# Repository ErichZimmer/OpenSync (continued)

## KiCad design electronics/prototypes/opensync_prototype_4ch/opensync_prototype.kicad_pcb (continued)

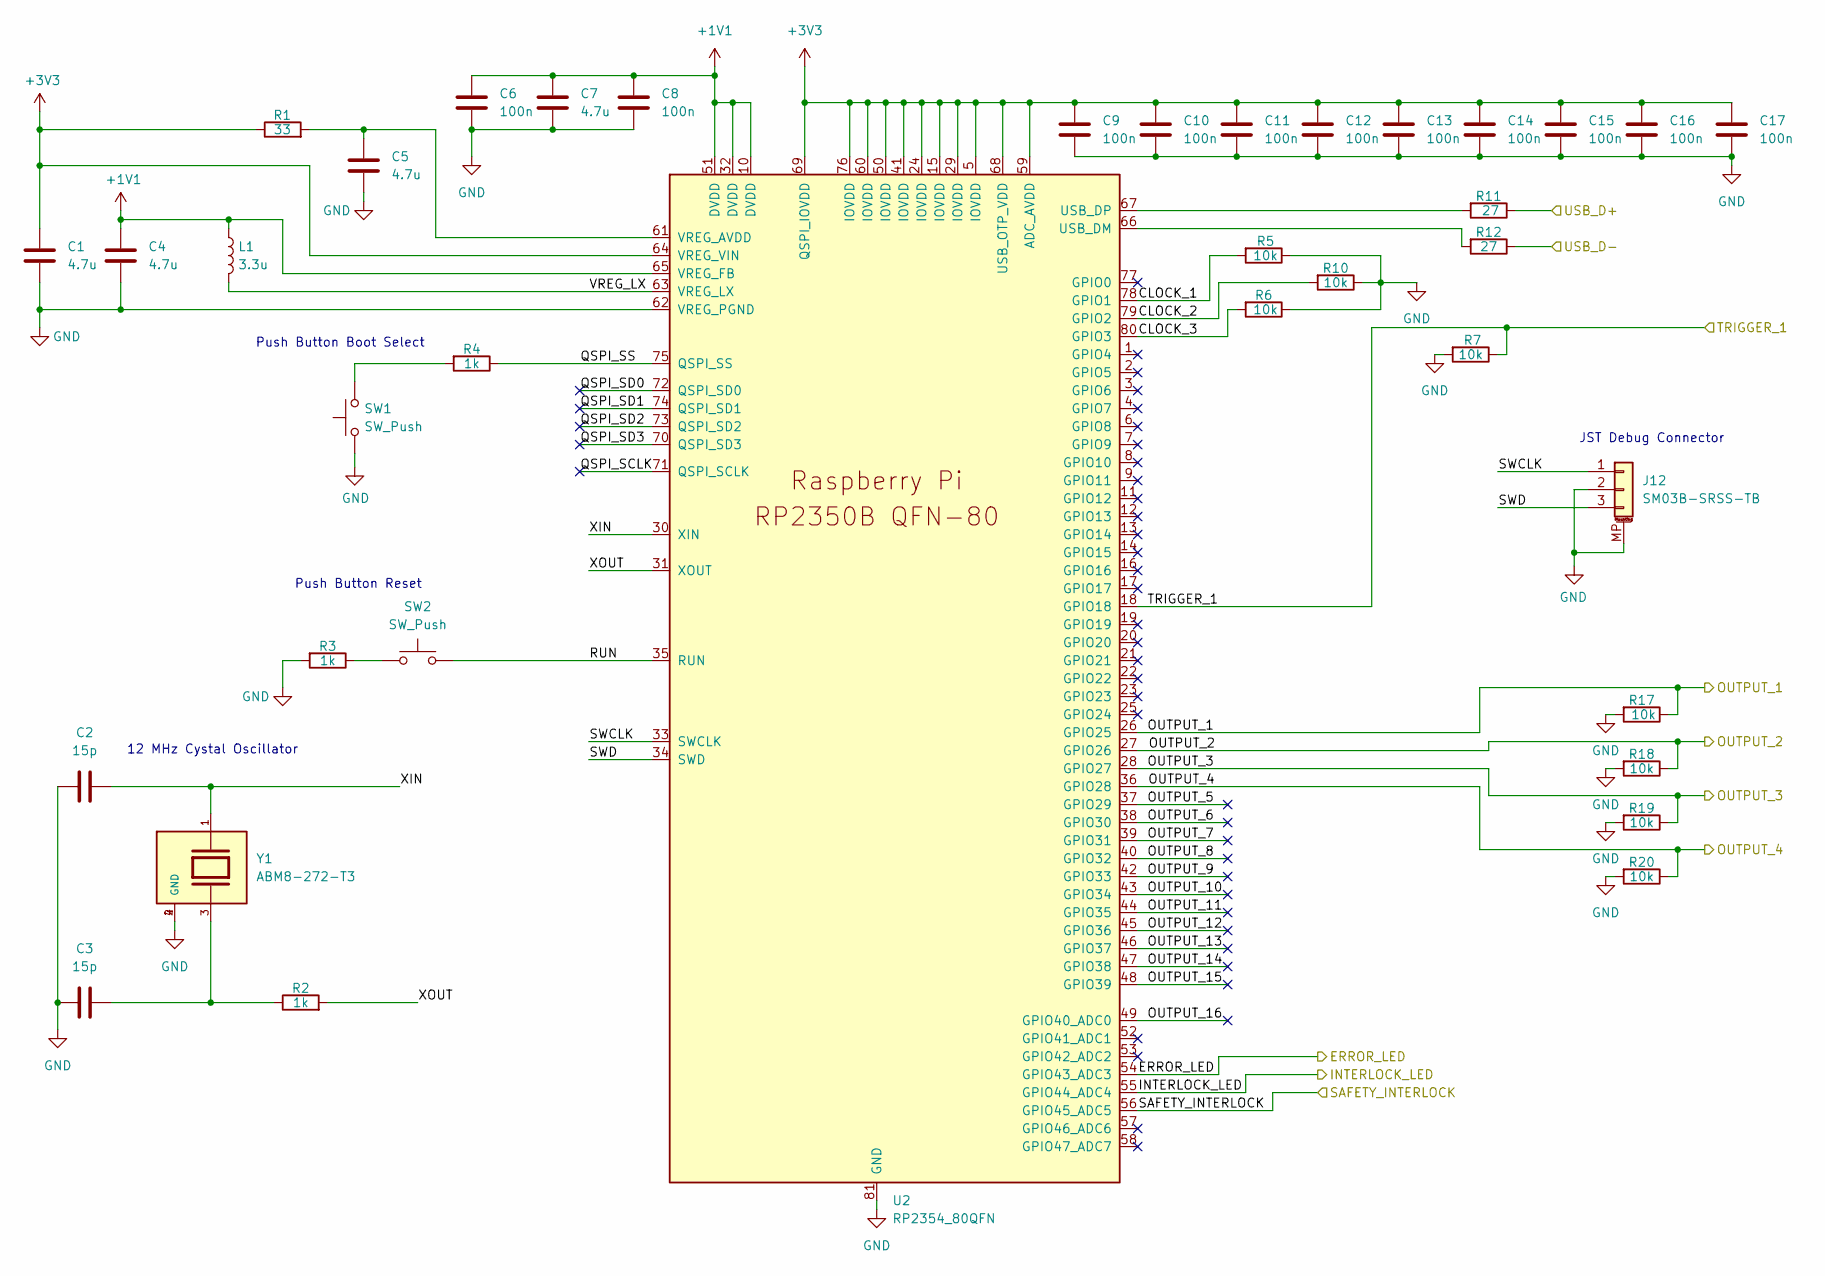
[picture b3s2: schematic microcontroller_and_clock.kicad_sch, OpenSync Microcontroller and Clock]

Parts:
C1, C4, C5: 4.7u; C_0402_1005Metric_small_pads; LCSC C326586
C2, C3: 15p; C_0402_1005Metric_small_pads; LCSC C326803
C6, C8, C9, C10, C11, C12, C13, C14, C15, C16, C17: 100n; C_0402_1005Metric_small_pads; LCSC C60474
C7: 4.7u; C_0402_1005Metric_small_pads; LCSC C60474
J12: SM03B-SRSS-TB; JST_SH_SM03B-SRSS-TB_1x03-1MP_P1.00mm_Horizontal; LCSC C160403
L1: 3.3u; L_pol_2016; LCSC C42411119
R1: 33; R_0402_1005Metric; LCSC C844506
R2, R3, R4: 1k; R_0402_1005Metric; LCSC C313354
R5, R6, R7, R10, R17, R18, R19, R20: 10k; R_0402_1005Metric; LCSC C71617
R11, R12: 27; R_0402_1005Metric; LCSC C4162575
SW1, SW2: SW_Push; SW_Push_1P1T_NO_Vertical_Wuerth_434133025816; LCSC C5504987
U2: RP2354_80QFN; RP2350-QFN-80-1EP_10x10_P0.4mm_EP3.4x3.4mm_ThermalVias; LCSC C39843328
Y1: ABM8-272-T3; XTAL_ABM8-272-T3; PARTREV 07-29-20; LCSC C20625731

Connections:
+1V1: C4.1, C6.1, C7.1, C8.1, L1.1, U2.10 (DVDD), U2.32 (DVDD), U2.51 (DVDD), U2.65 (VREG_FB)
+3V3: C1.1, C9.1, C10.1, C11.1, C12.1, C13.1, C14.1, C15.1, C16.1, C17.1, R1.1, U2.5 (IOVDD), U2.15 (IOVDD), U2.24 (IOVDD), U2.29 (IOVDD), U2.41 (IOVDD), U2.50 (IOVDD), U2.59 (ADC_AVDD), U2.60 (IOVDD), U2.64 (VREG_VIN), U2.68 (USB_OTP_VDD), U2.69 (QSPI_IOVDD), U2.76 (IOVDD); also elsewhere on the board
/LEDs and Interlock/ERROR_LED: U2.54 (GPIO43_ADC3); also elsewhere on the board
/LEDs and Interlock/INTERLOCK_LED: U2.55 (GPIO44_ADC4); also elsewhere on the board
/LEDs and Interlock/SAFETY_INTERLOCK: U2.56 (GPIO45_ADC5); also elsewhere on the board
/Microcontroller and Ext. Clock/CLOCK_1: R5.2, U2.78 (GPIO1)
/Microcontroller and Ext. Clock/CLOCK_2: R10.2, U2.79 (GPIO2)
/Microcontroller and Ext. Clock/CLOCK_3: R6.2, U2.80 (GPIO3)
/Microcontroller and Ext. Clock/OUTPUT_1: R17.1, U2.26 (GPIO25); also elsewhere on the board
/Microcontroller and Ext. Clock/OUTPUT_2: R18.1, U2.27 (GPIO26); also elsewhere on the board
/Microcontroller and Ext. Clock/OUTPUT_3: R19.1, U2.28 (GPIO27); also elsewhere on the board
/Microcontroller and Ext. Clock/OUTPUT_4: R20.1, U2.36 (GPIO28); also elsewhere on the board
/Microcontroller and Ext. Clock/OUTPUT_5: U2.37 (GPIO29)
/Microcontroller and Ext. Clock/OUTPUT_6: U2.38 (GPIO30)
/Microcontroller and Ext. Clock/OUTPUT_7: U2.39 (GPIO31)
/Microcontroller and Ext. Clock/OUTPUT_8: U2.40 (GPIO32)
/Microcontroller and Ext. Clock/OUTPUT_9: U2.42 (GPIO33)
/Microcontroller and Ext. Clock/OUTPUT_10: U2.43 (GPIO34)
/Microcontroller and Ext. Clock/OUTPUT_11: U2.44 (GPIO35)
/Microcontroller and Ext. Clock/OUTPUT_12: U2.45 (GPIO36)
/Microcontroller and Ext. Clock/OUTPUT_13: U2.46 (GPIO37)
/Microcontroller and Ext. Clock/OUTPUT_14: U2.47 (GPIO38)
/Microcontroller and Ext. Clock/OUTPUT_15: U2.48 (GPIO39)
/Microcontroller and Ext. Clock/OUTPUT_16: U2.49 (GPIO40_ADC0)
/Microcontroller and Ext. Clock/QSPI_SCLK: U2.71 (QSPI_SCLK)
/Microcontroller and Ext. Clock/QSPI_SD0: U2.72 (QSPI_SD0)
/Microcontroller and Ext. Clock/QSPI_SD1: U2.74 (QSPI_SD1)
/Microcontroller and Ext. Clock/QSPI_SD2: U2.73 (QSPI_SD2)
/Microcontroller and Ext. Clock/QSPI_SD3: U2.70 (QSPI_SD3)
/Microcontroller and Ext. Clock/QSPI_SS: R4.1, U2.75 (QSPI_SS)
/Microcontroller and Ext. Clock/RUN: SW2.2, U2.35 (RUN)
/Microcontroller and Ext. Clock/SWCLK: J12.1, U2.33 (SWCLK)
/Microcontroller and Ext. Clock/SWD: J12.3, U2.34 (SWD)
/Microcontroller and Ext. Clock/TRIGGER_1: R7.1, U2.18 (GPIO18); also elsewhere on the board
/Microcontroller and Ext. Clock/VREG_LX: L1.2, U2.63 (VREG_LX)
/Microcontroller and Ext. Clock/XIN: C2.2, U2.30 (XIN), Y1.1
/Microcontroller and Ext. Clock/XOUT: R2.2, U2.31 (XOUT)
/Power and Data/USB_D+: R11.1; also elsewhere on the board
/Power and Data/USB_D-: R12.1; also elsewhere on the board
GND: C1.2, C2.1, C3.1, C4.2, C5.2, C6.2, C7.2, C8.2, C9.2, C10.2, C11.2, C12.2, C13.2, C14.2, C15.2, C16.2, C17.2, J12.2, J12.MP (MountPin), R3.2, R5.1, R6.1, R7.2, R10.1, R17.2, R18.2, R19.2, R20.2, SW1.1, U2.62 (VREG_PGND), U2.81 (GND), Y1.2 (GND), Y1.4 (GND); also elsewhere on the board
unnamed: C3.2, R2.1, Y1.3
unnamed: R3.1, SW2.1
unnamed: R4.2, SW1.2
unnamed: R12.2, U2.66 (USB_DM)
unnamed: R11.2, U2.67 (USB_DP)
unnamed: C5.1, R1.2, U2.61 (VREG_AVDD)

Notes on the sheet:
12 MHz Cystal Oscillator
JST Debug Connector
Push Button Boot Select
Push Button Reset

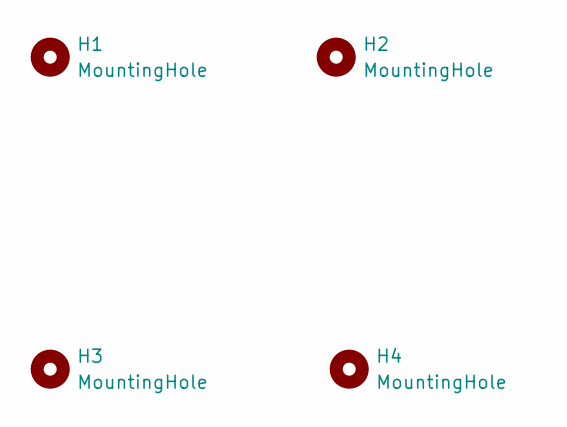
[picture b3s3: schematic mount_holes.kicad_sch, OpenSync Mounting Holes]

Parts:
H1, H2, H3, H4: MountingHole; MountingHole_3.2mm_M3_ISO7380

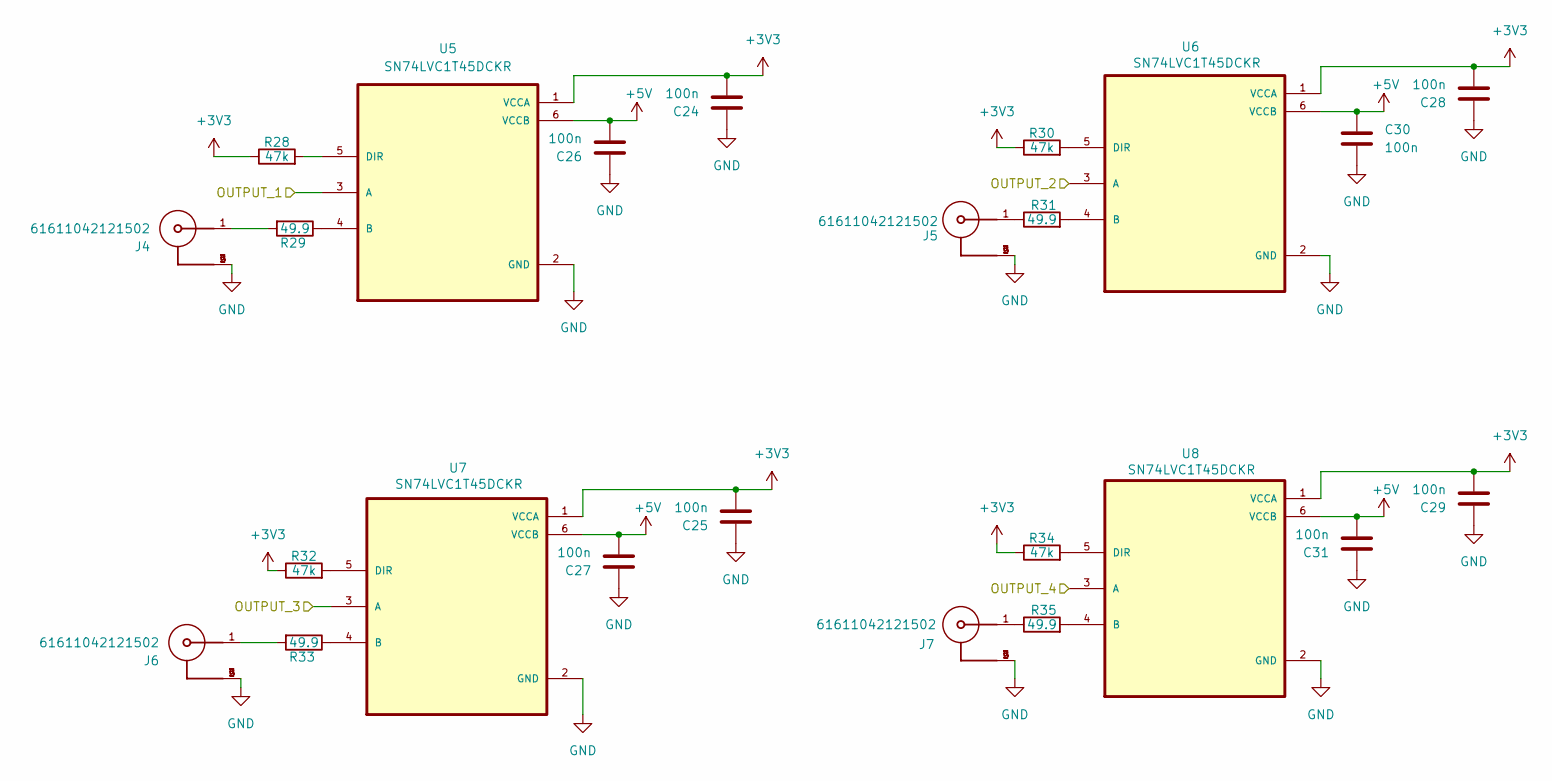
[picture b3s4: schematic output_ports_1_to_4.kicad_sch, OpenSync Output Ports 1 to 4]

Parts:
C24, C25, C26, C27, C28, C29, C30, C31: 100n; C_0402_1005Metric_small_pads; LCSC C60474
J4, J5, J6, J7: 61611042121502
R28, R30, R32, R34: 47k; R_0402_1005Metric; LCSC C176117
R29, R31, R33, R35: 49.9; R_0402_1005Metric; LCSC C1858992
U5, U6, U7, U8: SN74LVC1T45DCKR; SOT65P210X110-6N; LCSC C9382

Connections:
+3V3: C24.2, C25.2, C28.2, C29.2, R28.1, R30.1, R32.1, R34.1, U5.1 (VCCA), U6.1 (VCCA), U7.1 (VCCA), U8.1 (VCCA); also elsewhere on the board
+5V: C26.2, C27.2, C30.1, C31.2, U5.6 (VCCB), U6.6 (VCCB), U7.6 (VCCB), U8.6 (VCCB); also elsewhere on the board
/Microcontroller and Ext. Clock/OUTPUT_1: U5.3 (A); also elsewhere on the board
/Microcontroller and Ext. Clock/OUTPUT_2: U6.3 (A); also elsewhere on the board
/Microcontroller and Ext. Clock/OUTPUT_3: U7.3 (A); also elsewhere on the board
/Microcontroller and Ext. Clock/OUTPUT_4: U8.3 (A); also elsewhere on the board
GND: C24.1, C25.1, C26.1, C27.1, C28.1, C29.1, C30.2, C31.1, J4.2, J4.3, J4.4, J4.5, J5.2, J5.3, J5.4, J5.5, J6.2, J6.3, J6.4, J6.5, J7.2, J7.3, J7.4, J7.5, U5.2 (GND), U6.2 (GND), U7.2 (GND), U8.2 (GND); also elsewhere on the board
unnamed: J4.1, R29.2
unnamed: J5.1, R31.1
unnamed: J6.1, R33.2
unnamed: J7.1, R35.1
unnamed: R29.1, U5.4 (B)
unnamed: R28.2, U5.5 (DIR)
unnamed: R31.2, U6.4 (B)
unnamed: R30.2, U6.5 (DIR)
unnamed: R33.1, U7.4 (B)
unnamed: R32.2, U7.5 (DIR)
unnamed: R35.2, U8.4 (B)
unnamed: R34.2, U8.5 (DIR)

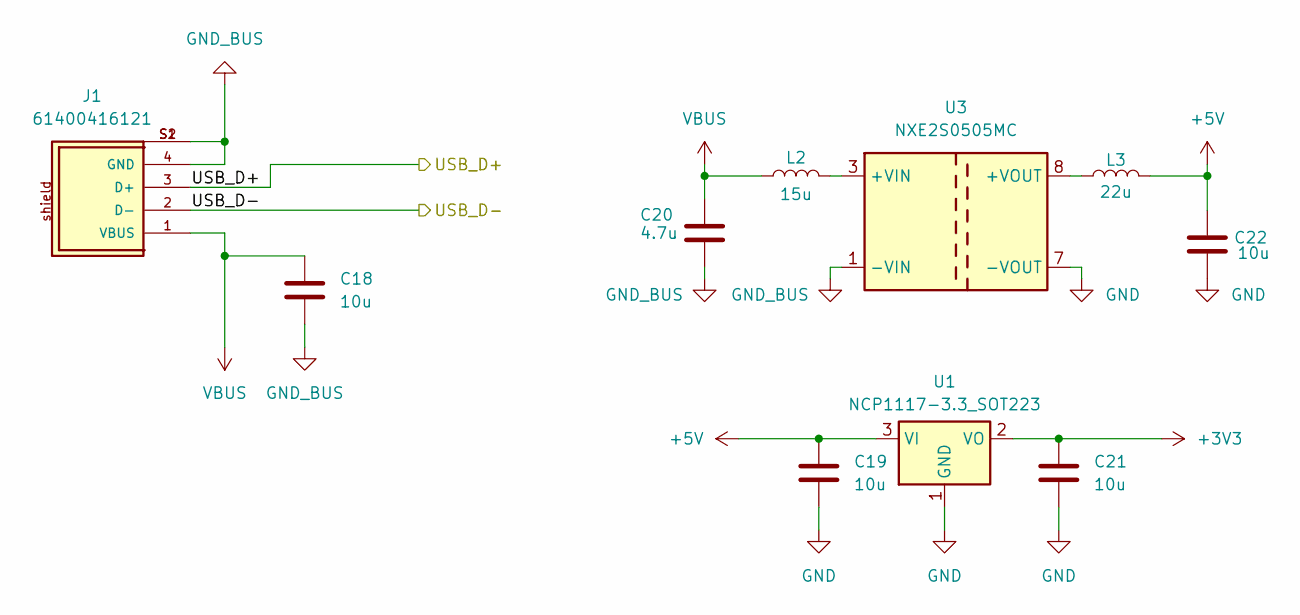
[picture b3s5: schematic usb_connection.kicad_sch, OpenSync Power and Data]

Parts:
C18, C19, C21, C22: 10u; C_0402_1005Metric_small_pads; LCSC C1856484
C20: 4.7u; C_0402_1005Metric_small_pads; LCSC C326586
J1: 61400416121
L2: 15u; IND_ASPI-4030S-150M-T; LCSC C5570254
L3: 22u; IND_ASPI6045S220MT; LCSC C187454
U1: NCP1117-3.3_SOT223; SOT-223-3_TabPin2; LCSC C26537
U3: NXE2S0505MC; Converter_DCDC_Murata_NXExSxxxxMC_SMD

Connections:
+3V3: C21.1, U1.2 (VO); also elsewhere on the board
+5V: C19.1, C22.1, L3.2, U1.3 (VI); also elsewhere on the board
/Power and Data/USB_D+: J1.3 (D+); also elsewhere on the board
/Power and Data/USB_D-: J1.2 (D-); also elsewhere on the board
GND: C19.2, C21.2, C22.2, U1.1 (GND), U3.7 (-VOUT); also elsewhere on the board
unnamed: L2.2, U3.3 (+VIN)
unnamed: L3.1, U3.8 (+VOUT)

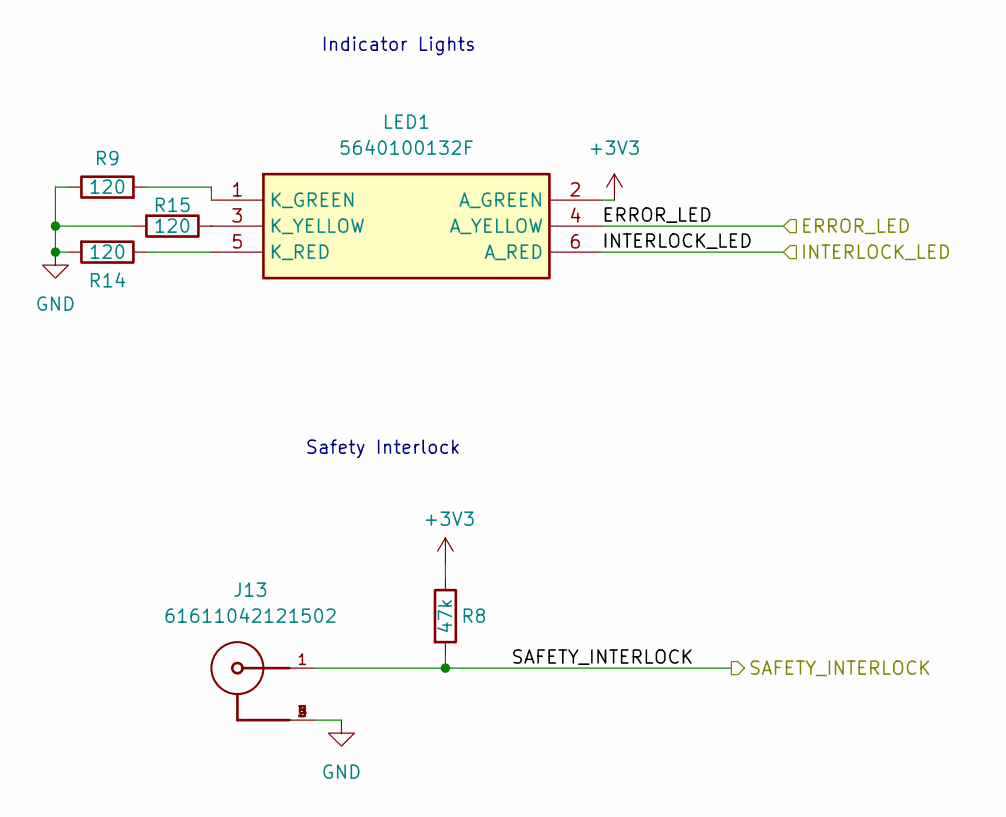
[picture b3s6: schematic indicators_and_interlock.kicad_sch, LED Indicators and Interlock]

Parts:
J13: 61611042121502
LED1: 5640100132F; Manufacturer_Part_Number 5640100132F
R8: 47k; R_0402_1005Metric; LCSC C176117
R9, R14, R15: 120; R_0402_1005Metric; LCSC C2100747

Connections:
+3V3: LED1.2 (A_GREEN), R8.1; also elsewhere on the board
/LEDs and Interlock/ERROR_LED: LED1.4 (A_YELLOW); also elsewhere on the board
/LEDs and Interlock/INTERLOCK_LED: LED1.6 (A_RED); also elsewhere on the board
/LEDs and Interlock/SAFETY_INTERLOCK: J13.1, R8.2; also elsewhere on the board
GND: J13.2, J13.3, J13.4, J13.5, R9.1, R14.2, R15.2; also elsewhere on the board
unnamed: LED1.1 (K_GREEN), R9.2
unnamed: LED1.5 (K_RED), R14.1
unnamed: LED1.3 (K_YELLOW), R15.1

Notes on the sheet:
Safety Interlock
Indicator Lights

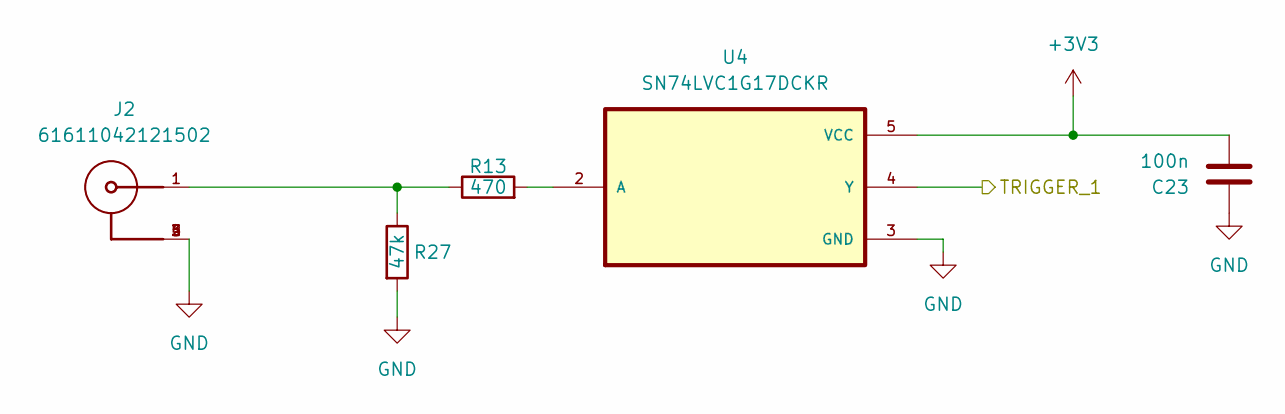
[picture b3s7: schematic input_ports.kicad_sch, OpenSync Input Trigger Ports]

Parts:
C23: 100n; C_0402_1005Metric_small_pads; LCSC C60474
J2: 61611042121502
R13: 470; R_0402_1005Metric; LCSC C482182
R27: 47k; R_0402_1005Metric; LCSC C176117
U4: SN74LVC1G17DCKR; SOT65P210X110-5N; DigiKey_Part_Number 296-11934-1-ND

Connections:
+3V3: C23.1, U4.5 (VCC); also elsewhere on the board
/Microcontroller and Ext. Clock/TRIGGER_1: U4.4 (Y); also elsewhere on the board
GND: C23.2, J2.2, J2.3, J2.4, J2.5, R27.2, U4.3 (GND); also elsewhere on the board
unnamed: J2.1, R13.1, R27.1
unnamed: R13.2, U4.2 (A)

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
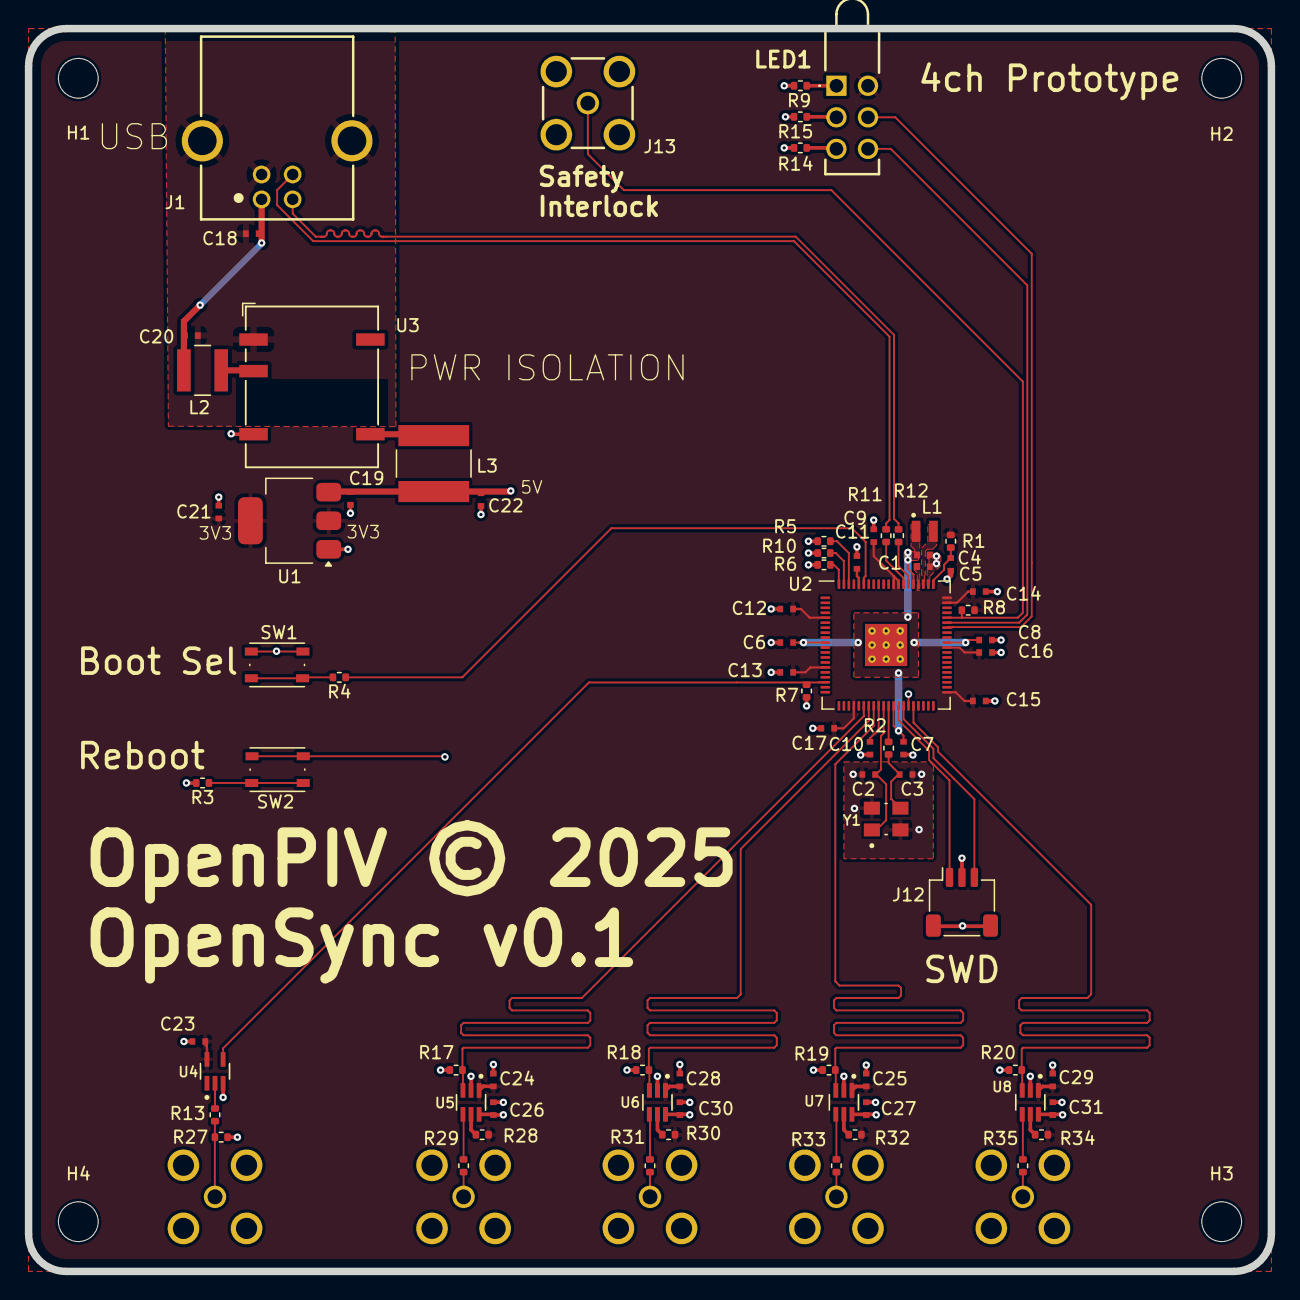
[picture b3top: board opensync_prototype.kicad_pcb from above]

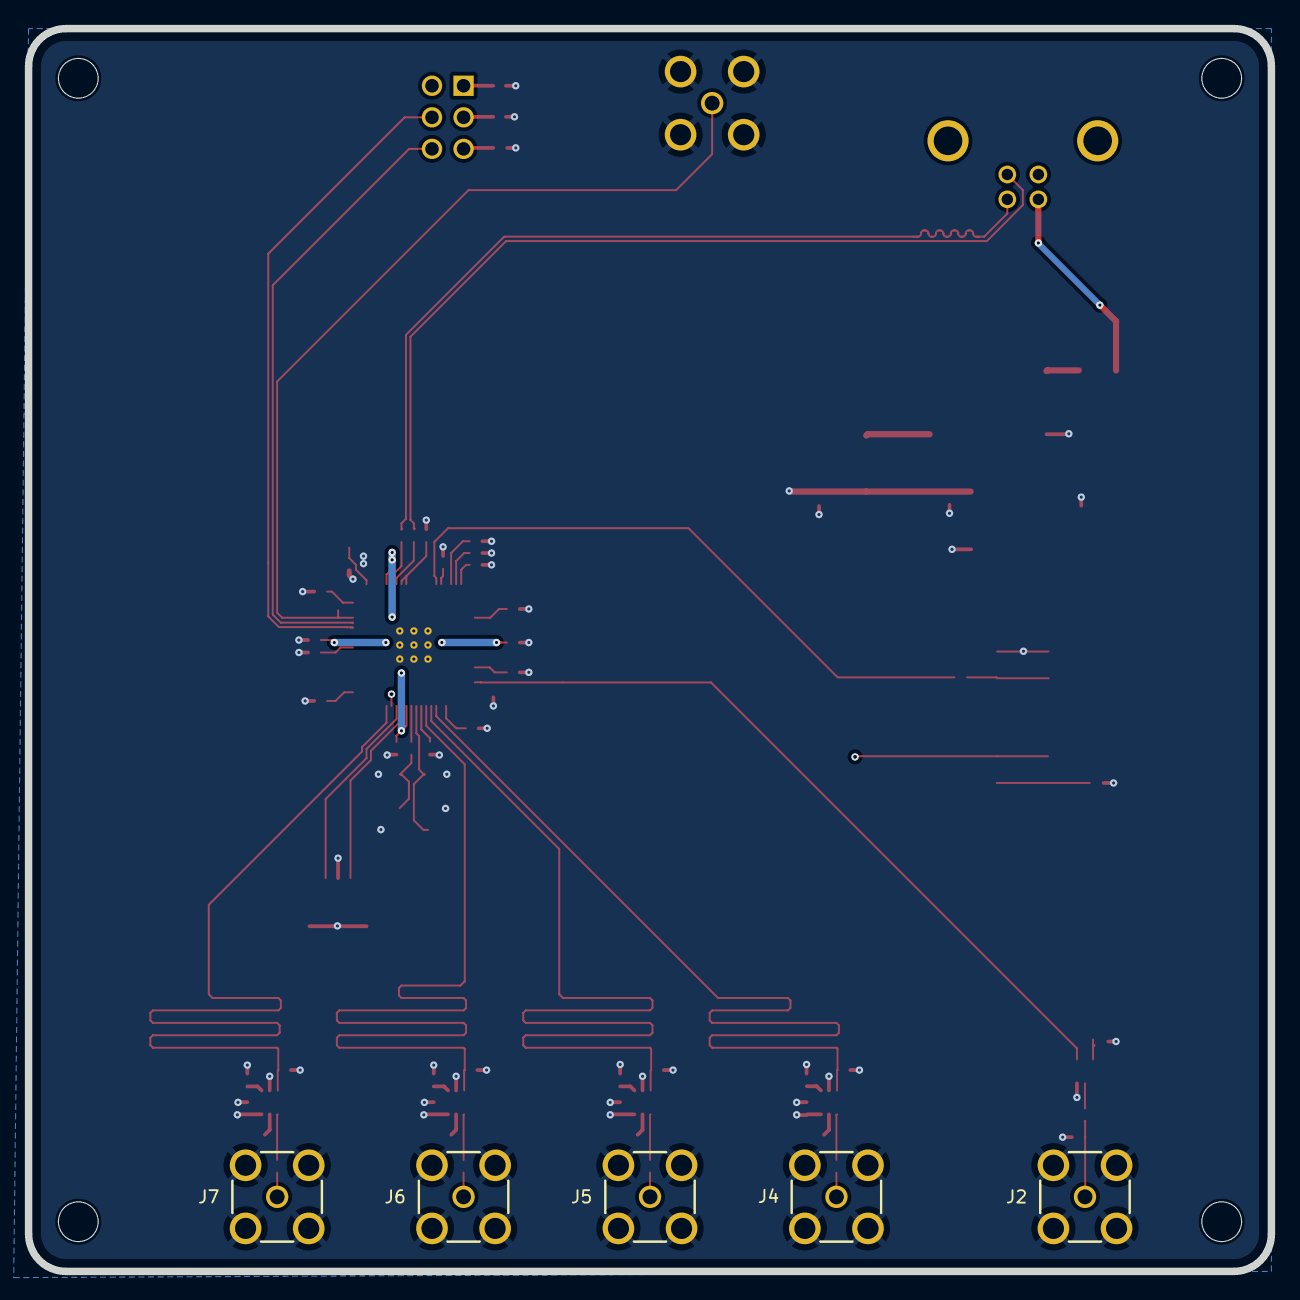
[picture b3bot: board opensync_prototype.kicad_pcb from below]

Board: 4 copper layers, 100.0 x 100.0 mm, 86 parts (5 on the bottom side), 51 nets.

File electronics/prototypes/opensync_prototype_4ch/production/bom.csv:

Designator,Footprint,Quantity,Value,LCSC Part #
"C1, C20, C4, C5",0402,4,4.7u,C326586
"C10, C11, C12, C13, C14, C15, C16, C17, C23, C24, C25, C26, C27, C28, C29, C30, C31, C6, C8, C9",0402,20,100n,C60474
"C18, C19, C21, C22",0402,4,10u,C1856484
"C2, C3",0402,2,15p,C326803
C7,0402,1,4.7u,C60474
"D1, D2",0603,2,LED,
J1,61400416121,1,61400416121,
J12,JST_SH_SM03B-SRSS-TB_1x03-1MP_P1.00mm_Horizontal,1,SM03B-SRSS-TB,
"J13, J2, J4, J5, J6, J7",61611042121502,6,61611042121502,
L1,L_pol_2016,1,3.3u,C42411119
L2,IND_ASPI-4030S-150M-T,1,15u,C5570254 
L3,IND_ASPI6045S220MT,1,22u,C187454
R1,0402,1,33,C844506
"R10, R17, R18, R19, R20, R5, R6, R7",0402,8,10k,C71617
"R11, R12",0402,2,27,C4162575
R13,0402,1,470,C482182
R14,0402,1,100,
"R2, R3, R4",0402,3,1k,C313354
"R27, R28, R30, R32, R34, R8",0402,6,47k,C176117
"R29, R31, R33, R35",0402,4,49.9,C1858992
R9,0402,1,169,
"SW1, SW2",SW_Push_1P1T_NO_Vertical_Wuerth_434133025816,2,SW_Push,
U1,SOT-223-3_TabPin2,1,NCP1117-3.3_SOT223,C26537
U2,RP2350-QFN-80-1EP_10x10_P0.4mm_EP3.4x3.4mm_ThermalVias,1,RP2354_80QFN,C39843328
U3,Converter_DCDC_Murata_NXExSxxxxMC_SMD,1,NXE2S0505MC,
U4,SOT65P210X110-5N,1,SN74LVC1G17DCKR,C10425
"U5, U6, U7, U8",SOT65P210X110-6N,4,SN74LVC1T45DCKR,C9382
Y1,XTAL_ABM8-272-T3,1,ABM8-272-T3,C20625731

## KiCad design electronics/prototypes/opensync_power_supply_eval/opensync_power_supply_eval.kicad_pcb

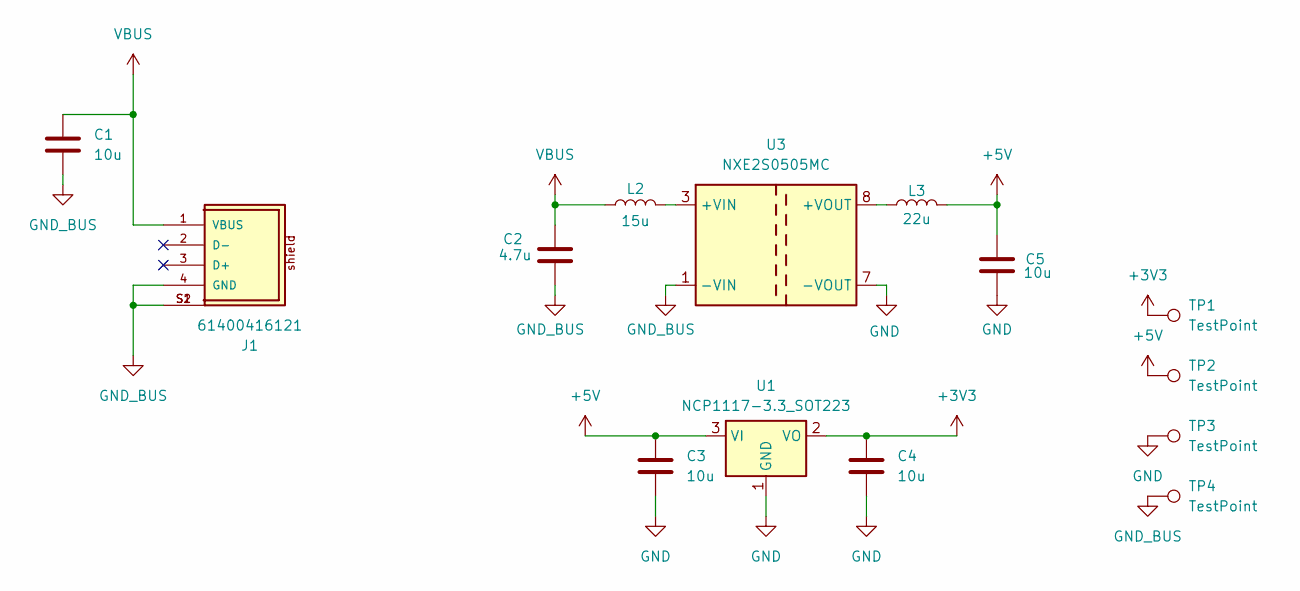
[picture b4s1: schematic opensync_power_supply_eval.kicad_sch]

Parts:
C1, C3, C4, C5: 10u; C_0402_1005Metric_small_pads; LCSC C1856484
C2: 4.7u; C_0402_1005Metric_small_pads; LCSC C326586
J1: 61400416121
L2: 15u; IND_ASPI-4030S-150M-T; LCSC C5570254
L3: 22u; IND_ASPI6045S220MT; LCSC C187454
TP1, TP2, TP3, TP4: TestPoint; TestPoint_Pad_2.0x2.0mm
U1: NCP1117-3.3_SOT223; SOT-223-3_TabPin2; LCSC C26537
U3: NXE2S0505MC; Converter_DCDC_Murata_NXExSxxxxMC_SMD

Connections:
+3V3: C4.1, TP1.1, U1.2 (VO)
+5V: C3.1, C5.1, L3.2, TP2.1, U1.3 (VI)
GND: C3.2, C4.2, C5.2, TP3.1, U1.1 (GND), U3.7 (-VOUT)
GND_BUS: C1.1, C2.1, J1.4 (GND), J1.S1, J1.S2, TP4.1, U3.1 (-VIN)
unnamed: L2.2, U3.3 (+VIN)
unnamed: L3.1, U3.8 (+VOUT)
VBUS: C1.2, C2.2, J1.1 (VBUS), L2.1

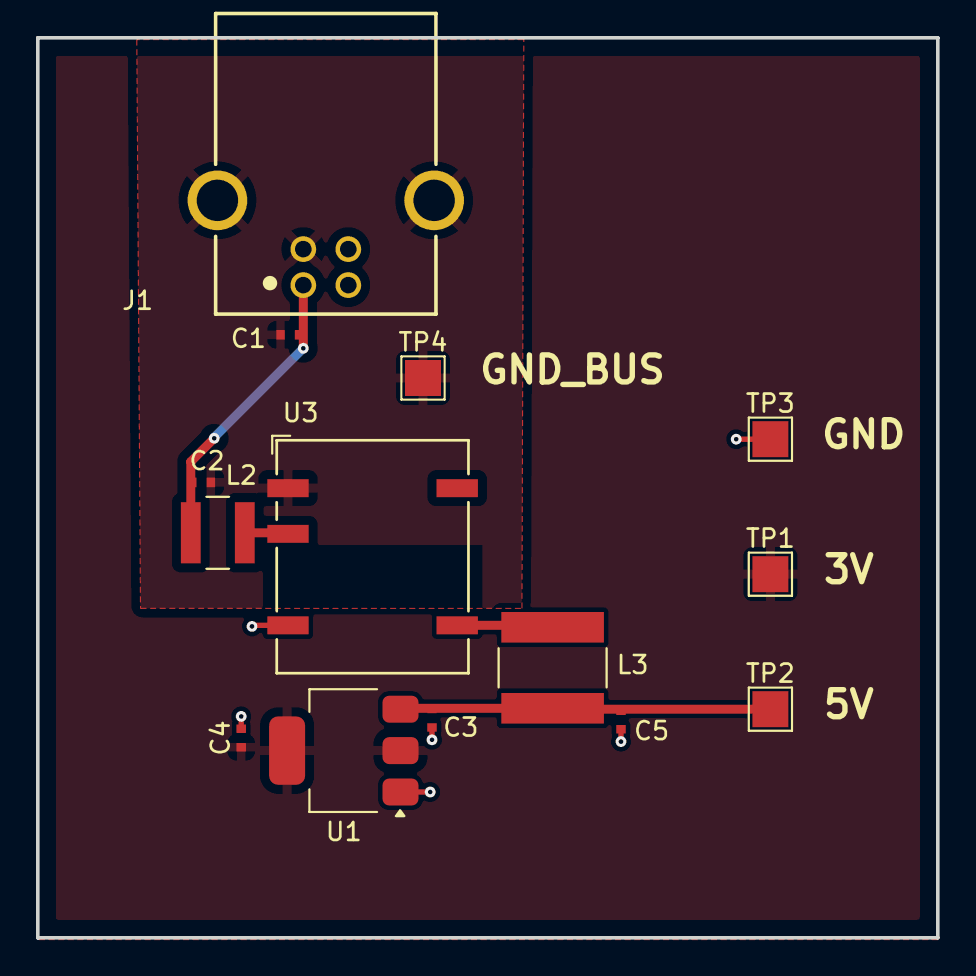
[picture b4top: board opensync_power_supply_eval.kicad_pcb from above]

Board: 2 copper layers, 50.0 x 50.0 mm, 14 parts (0 on the bottom side), 7 nets.

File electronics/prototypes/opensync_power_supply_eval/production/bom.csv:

Designator,Footprint,Quantity,Value,LCSC Part #
"C1, C3, C4, C5",0402,4,10u,C1856484
C2,0402,1,4.7u,C326586
J1,61400416121,1,61400416121,
L2,IND_ASPI-4030S-150M-T,1,15u,C5570254 
L3,IND_ASPI6045S220MT,1,22u,C187454
"TP1, TP2, TP3, TP4",TestPoint_Pad_2.0x2.0mm,4,TestPoint,
U1,SOT-223-3_TabPin2,1,NCP1117-3.3_SOT223,C26537
U3,Converter_DCDC_Murata_NXExSxxxxMC_SMD,1,NXE2S0505MC,

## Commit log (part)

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2024-04-25 Update README.md
    - Add FPGA synchronizer to possible solutions
2025-04-05 Update README.md
    - Switched to RP2350 microcontroller
2025-04-30 Update README.md
    - Did basic update for now.
    - I also am still waiting on that Oscilloscope....
2025-05-02 Update README.md
    - Spiced some things up a little.
    - Still waiting on that oscilloscope. It's been stuck in customs and seems like its going to be a return to shipper??
2025-05-15 Update README.md
    - 24 Output channels pulled too much power to function properly.
    - Output channels were reduced to a maximum of 16 channels.
    - Added basic compilation information.
2025-05-18 Update to code base
2025-05-18 Ambiguity in which pico sdk is being linked to
2025-05-18 Forgot architecture tree
2025-05-18 No idea what happened
2025-05-18 Enabled a demo image
2025-05-18 Update README.md
    - Messed up relative import
2025-05-20 Added a better demo image
2025-05-20 Added the software files (exc. docs) to public repo
2025-05-20 Oops
2025-05-25 Some extra quick work
2025-05-25 Update README.md
    - Some typos and organization issues
2025-05-26 Bug fixes
2025-05-26 Updated project bio
2025-05-26 Update README.md
    - I meant for there to be 4 internal synchronization clocks, not 2. 2 would be better since there will only be 2 input channels for external triggers, but 4 will be just as easy to implement due to t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
2025-05-26 Update README.md
    - Forgot to mention that I now change system clock instead of using pio_sm_clock_divider (or something along those lines)
2025-05-26 Update README.md
    - I plan on making public the private systems development life cycle documentation (.docx and .pdf file)
2025-05-27 Update README.md
    - Added errata 9 for RP2350 A2 chip
2025-05-27 Ran out of GPIO pins, Oops.
2025-05-28 I fixed it!!
    - Apparently, PIO blocks can spy on outputs passively. There is a 4 cycle jitter compared to 2 cycles for an external trigger, but hey, it works!!
    - This frees up 4 pins that can now go back to output channels (12 -> 16)
2025-05-28 Backup SDLC public documents
2025-05-28 Wrong extension
2025-05-29 Updated SDLC
2025-05-29 Grammar
2025-05-29 Added disclaimer
2025-05-29 Branched SDLC dir
2025-05-29 Rename briefing
2025-05-29 Added stage 1 SDLC
2025-05-30 Elaborated on proposed solution
2025-06-01 Upgraded clock frequency
2025-06-03 Broke mcu, spelling fixes
2025-06-08 Updated design
2025-06-08 Updated SDLC feasibility
2025-06-08 Updated briefing
2025-06-10 Updated study
2025-06-10 Update README.md
    - Fixed some things.
2025-06-13 Emergency push (bad storms coming)
2025-06-13 Obsolete file
2025-09-02 Update project schedule due to internship conflicts
2025-09-02 Update README.md for new project scheduling
2025-09-02 Update briefing.md
    - There are now three input channels and internal clocks
2025-09-07 Initial assembly design
2025-09-07 Wrong file, oops
2025-09-07 Bug fix
2025-09-07 Rename folder
2025-09-07 Oops, brainfog alert
2025-09-07 Spelling fix
2025-09-07 Empty directory for later
2025-09-07 Updated licensing
2025-09-07 Redone licensing
2025-09-08 Make sure sysclk is a multiple of 48
2025-09-08 Reset TODO list; rewriting OpenSync
2025-09-09 Initial status design
2025-09-09 Renamed some stuff
2025-09-09 Oops, forgot to save
2025-09-09 Added structs
2025-09-09 Some functionality at least
2025-09-09 Prawn DO forgot header guard
2025-09-10 Added timing graphs
2025-09-10 Updated flowchart
2025-09-10 Re-organized directory
2025-09-11 Add sections and revised funding
2025-09-11 Added figure numbers
2025-09-12 Initial multicore template
2025-09-12 Sequencer stuff
2025-09-12 Some touchups
2025-09-12 Fixed pragma once
2025-09-13 Initial sequencer output design
2025-09-14 Renamed to something better
2025-09-14 Forgot about program offsets
2025-09-14 Emergency push: Bad weather?
2025-09-16 Supress Prawn DO TUSB warnings
2025-09-16 Updated software
2025-09-16 Initial test (failed)
2025-09-19 Tried some fixes
2025-09-19 Typos
2025-09-23 Run 2: failed
2025-09-25 Fixed logic error (Tests passed)
2025-09-28 Safety push: Computer making weird noises
2025-09-28 15 minute break
2025-09-30 30 minute break
2025-09-30 Some extras
2025-10-01 Updated error handeling
2025-10-01 Reverted pio program
2025-10-01 Updated pulse output sm
2025-10-01 Updated new clock freq
2025-10-01 Updated TO-DO list
2025-10-01 Updated schedule
2025-10-02 Fixed some stuff
2025-10-02 Overclocking
2025-10-02 Testing new debug message function
2025-10-03 Some refactoring
2025-10-03 Code Asthetics (More mobile friendly)
2025-10-03 Refactoring (There's a stick bug on me!!)
2025-10-03 Refactor/Additions
2025-10-03 Lunch is over :(
2025-10-04 Some stuff
2025-10-04 Some fixes
2025-10-04 Updates software
2025-10-04 15 minute break is over
2025-10-04 15 minute break :(
2025-10-05 Initial KiCAD push
2025-10-05 Touched up some docs
2025-10-05 Added crystal specs
2025-10-15 Finally got motivated again (had a back injury)
2025-10-15 Phone push :)
2025-10-16 Fixed bugs with testing
2025-10-17 Add upper-ish bound of PLL jitter
2025-10-17 Fixed logic error
2025-10-17 Quick notebook on device
2025-10-17 Another basic and quickly done notebook
2025-10-17 Refactored header files
2025-10-17 Fixed clock divider debug
2025-10-17 Flattened print statement
2025-10-17 Fixed typo
2025-10-17 Updated notebook
2025-10-17 Restarted notebook
2025-10-17 Standardized output
2025-10-17 Increased pulse instruction buffer size
2025-10-18 Ensure vreg stability
2025-10-18 Type enforcement
2025-10-18 Force output and clock states to low
2025-10-20 Updated firmware
2025-10-20 Updated software/bug fixes
2025-10-20 Forgot init func
2025-10-21 Timing stuff
2025-10-22 Refactor
2025-10-24 Emergency push: Windows 11 update messed up my computer
2025-10-24 Osciliscope just came in the mail
2025-10-24 Removed LED power button due to costs
2025-10-25 Update vers
2025-10-25 Forced output low during abort
2025-10-25 Fixed clock types issue
2025-10-26 Add first mini milestone
2025-10-26 Video fix
2025-10-26 Manually uploaded video
2025-10-26 Updated to 64 inst.
2025-10-26 Timing fix
2025-10-26 Fixed buffer alignment issue
2025-10-26 Clock off by one issue
2025-10-26 Fix clock buffer alignment
2025-10-26 Aligned for aesthetics
2025-10-26 Fixed free issue
2025-10-26 Fixed iterate by 1
2025-10-27 Uncommented PIO labels
2025-10-27 Reset clock type
2025-10-27 Updated gitignore
2025-10-27 Forgot .vscode in firmware
2025-10-31 Started on schematica again
2025-11-01 Backup push
2025-11-01 Blank FreeCAD document
2025-11-02 Ignore KiCAD backups
2025-11-03 Fixed ring buffer
2025-11-05 Forgot to uncomment
2025-11-05 KiCAD backup
2025-11-10 Emergency backup
2025-11-10 Ignore zip files
2025-11-11 Backup copy
2025-11-11 Delete electronics/opensync_prototype/opensync_prototype-backups directory
    - This is not needed in the repo
2025-11-13 Updated jitter timing
2025-11-13 Max clock divider is 65500
2025-11-19 Backup
2025-12-02 Updated PCB design
2025-12-06 Fixed component placement
2025-12-13 Updated basic datasheet
2025-12-13 PCB rework
2025-12-14 PCB trace routes
2025-12-15 Hotel backup
2025-12-15 Trace routing and vias
2025-12-15 Routed buttons
2025-12-15 Somewhat tighter trace matching
2025-12-15 Updated board stackup
2025-12-15 Impedance matching
2025-12-16 Updated fills
2025-12-16 Rearranged some stuff
2025-12-16 Moved LED indicators
2025-12-21 GFround and power plane rework
2025-12-21 Fixed RF jack problems and LED sketch
2025-12-21 Increased spacing for output traces
2025-12-21 Fixed all DRC violations
2025-12-24 PCB touch-ups
2025-12-24 Increased pwr/gnd trace width
2025-12-24 Updated cooper pours
2025-12-24 Fixed USB CAD render
2025-12-24 PCB shenanigans
2025-12-24 USB footprint edit
2025-12-24 Gerber test
2025-12-28 Refined PCB
2025-12-29 Low cost 4ch prototype
2025-12-29 Added gerber files
2025-12-29 PCB trace refinement
2025-12-30 4ch PCB fixup
2025-12-31 Revised clock dividers
2025-12-31 Add clock divider to readme
2026-01-01 12 --> 16 ch design
2026-01-01 Included PCB design in SDLC
2026-01-01 Updated todo list
2026-01-05 Added part numbers
2026-01-05 Added more part numbers/updated PCB
2026-01-09 More prototyping
2026-01-13 Finalized dev power PCB
2026-01-13 Incl. SCPI parser library
2026-01-16 Hastily implemenmted scpi and finilaized PCB
2026-01-16 removed scpi-parser library
2026-01-16 Added scpi-parser as submodule for prototype
2026-01-16 Fixed naming fuckup
2026-01-16 Forgot to incl. trigger reps in output
2026-01-16 Reformatting
2026-01-16 Accredation issue
2026-01-16 Fixed bug in clock reset
2026-01-17 More bug fixes
2026-01-17 Ugly fix
2026-01-17 Format fix
2026-01-17 Updated python to scpi interface
2026-01-17 Refactored code
2026-01-17 Changed SCPI error no.
2026-01-17 Changed another error no.
2026-01-17 Software fixes
2026-01-17 Fresh start
2026-01-17 Fresh start (again)
2026-01-17 Slight output refactor
2026-01-17 Reduced pulse channels to 8
2026-01-17 Refined datasheet
2026-01-18 Fixed clock div naming
2026-01-18 Protected source dirs from import
2026-01-18 Refactored clock div
2026-01-19 Refactored clock type interface
2026-01-19 Refactored clock res options
2026-01-21 Units for pulse sequencer + 2.5 shots of tequila
2026-01-21 I don't remember doing any of this
2026-01-21 Added licenses png
2026-01-21 Moved copyright images to be bottom
2026-01-21 Better png image
2026-01-21 Fixed notes from drunk me
2026-01-22 Updated datasheet based on physical data
2026-01-22 Oops, meant 4 seconds
2026-01-22 Moved image to assets folder
2026-01-22 Moved other files to assets
2026-01-22 Fixed dir issue
2026-01-23 Added dat conversion to clock sequencer
2026-01-23 CLR --> CLEar
2026-01-23 Added conversion to nanoseconds fro mcycles
2026-01-23 Uncommented reset function
2026-01-23 Updated clock sequencer
2026-01-23 Fixed missing header
2026-01-24 Fixed clock conversion
2026-01-24 Untested (and not working) SCPI command update
2026-01-24 Set ringer buffer size automatically
2026-01-24 Reduced pulce isntruction pairs to 16
2026-01-24 Tidy up some things
2026-01-24 Just to be conservative
2026-01-24 Inconsistency
2026-01-24 Added buffer read check
2026-01-25 Finished on-device conversions
2026-01-25 Shoddy attempt to push w/o power and on solar panels
2026-01-26 Final push before battery dies
2026-01-28 Push after power back on and mornign worth of work
2026-01-28 Bus contention fix
2026-01-28 Forgot reset command
2026-01-28 SCPI command doc refactor
2026-01-28 Resolution --> Divider
2026-01-28 Datasheet correction
2026-03-05 Updated library
2026-04-02 Update on status
2026-06-07 Backup before storm
2026-06-22 Backup after first PIV experiment
